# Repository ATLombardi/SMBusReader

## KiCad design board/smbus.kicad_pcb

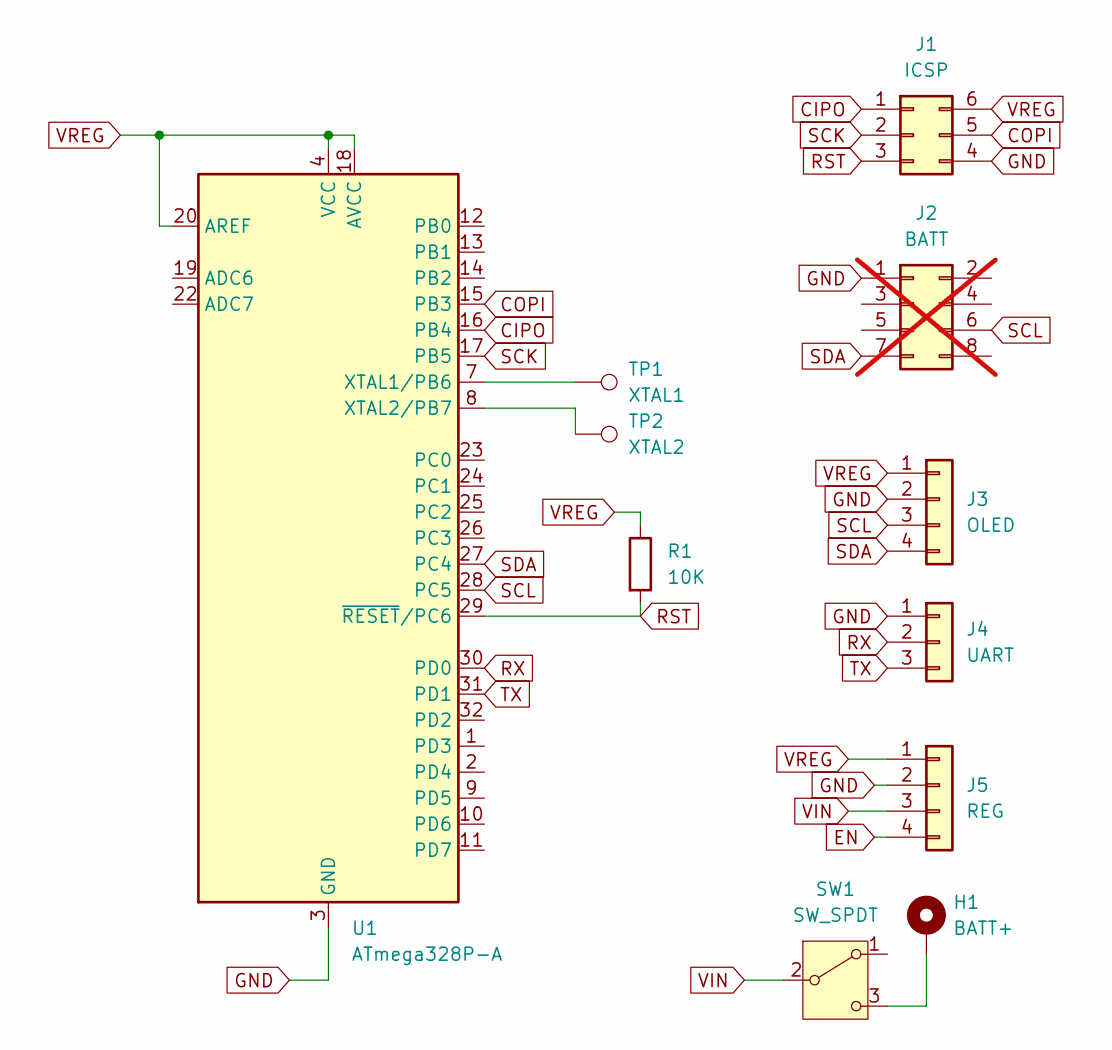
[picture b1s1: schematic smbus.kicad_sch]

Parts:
H1: BATT+; MountingHole_2.5mm_Pad
J1: ICSP; PinHeader_2x03_P2.54mm_Vertical; LCSC Part Number C65114
J2: BATT; PinHeader_2x04_P2.54mm_Vertical; not fitted
J3: OLED; PinSocket_1x04_P2.54mm_Vertical; LCSC Part Number C2905415
J4: UART; PinHeader_1x03_P2.54mm_Vertical; LCSC Part Number C5116482
J5: REG; PinSocket_1x04_P2.54mm_Vertical; LCSC Part Number C2905415
R1: 10K; R_1206_3216Metric; LCSC Part Number C17902
SW1: SW_SPDT; SW_Slide_SPDT_Angled_CK_OS102011MA1Q; LCSC Part Number C431547
TP1: XTAL1; TestPoint_Pad_1.0x1.0mm
TP2: XTAL2; TestPoint_Pad_1.0x1.0mm
U1: ATmega328P-A; TQFP-32_7x7mm_P0.8mm; LCSC Part Number C14877

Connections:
CIPO: J1.1, U1.16 (PB4)
COPI: J1.5, U1.15 (PB3)
EN: J5.4
GND: J1.4, J2.1, J3.2, J4.1, J5.2, U1.3 (GND), U1.5 (GND), U1.21 (GND)
unnamed: H1.1, SW1.3 (C)
unnamed: TP1.1, U1.7 (XTAL1/PB6)
unnamed: TP2.1, U1.8 (XTAL2/PB7)
RST: J1.3, R1.2, U1.29 (~RESET/PC6)
RX: J4.2, U1.30 (PD0)
SCK: J1.2, U1.17 (PB5)
SCL: J2.6, J3.3, U1.28 (PC5)
SDA: J2.7, J3.4, U1.27 (PC4)
TX: J4.3, U1.31 (PD1)
VIN: J5.3, SW1.2 (B)
VREG: J1.6, J3.1, J5.1, R1.1, U1.4 (VCC), U1.6 (VCC), U1.18 (AVCC), U1.20 (AREF)

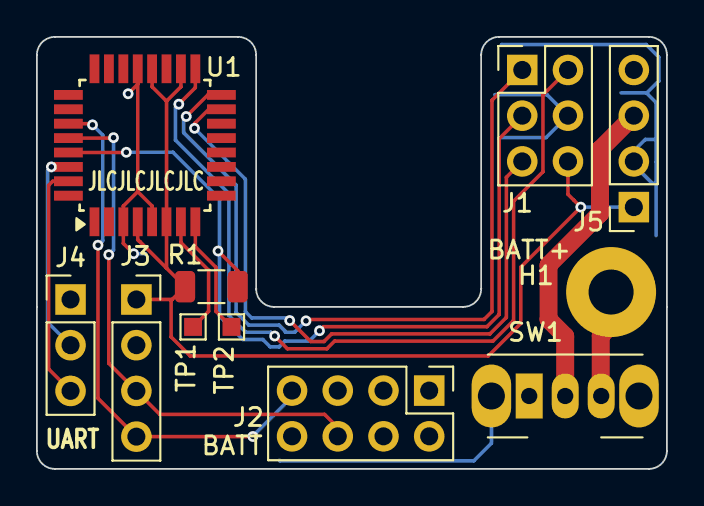
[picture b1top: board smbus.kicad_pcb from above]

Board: 2 copper layers, 35.0 x 24.0 mm, 11 parts (0 on the bottom side), 14 nets.

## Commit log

2024-04-28 First publish
2024-04-28 Assembly PDF for easier reading
2024-05-04 Fixed a bug with amperage display
